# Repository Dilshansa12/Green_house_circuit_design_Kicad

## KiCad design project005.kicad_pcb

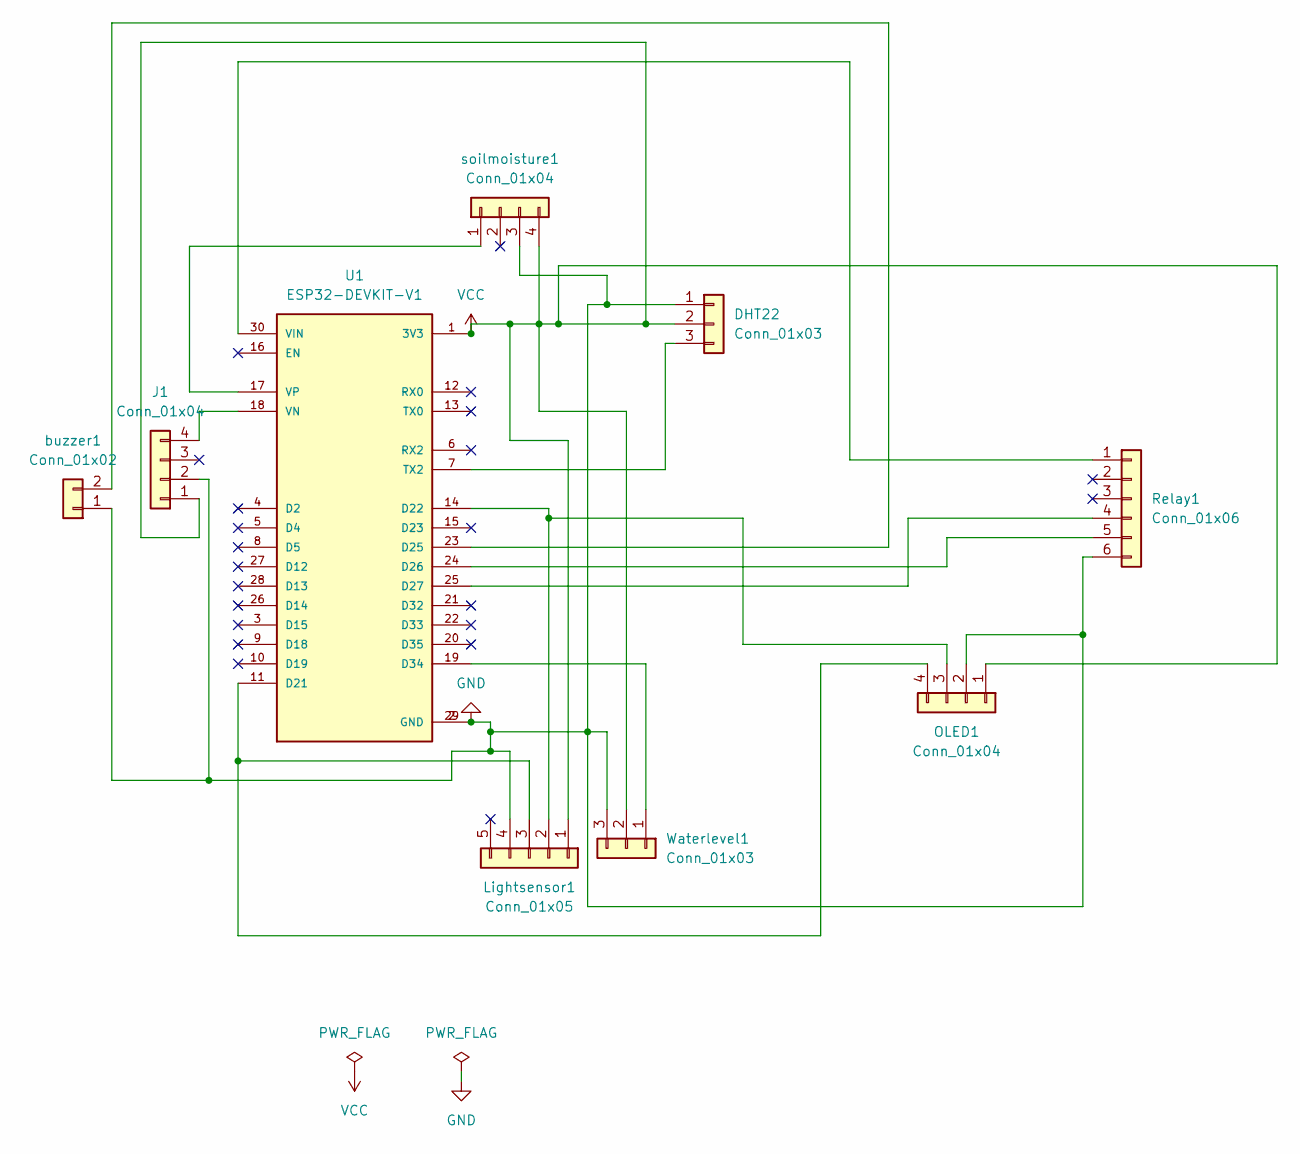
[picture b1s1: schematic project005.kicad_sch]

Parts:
DHT22: Conn_01x03; PinSocket_1x03_P2.54mm_Vertical
J1: Conn_01x04; PinSocket_1x04_P2.54mm_Vertical
Lightsensor1: Conn_01x05; PinSocket_1x05_P2.54mm_Vertical
OLED1: Conn_01x04; PinSocket_1x04_P2.54mm_Vertical
Relay1: Conn_01x06; PinSocket_1x06_P2.54mm_Vertical
U1: ESP32-DEVKIT-V1; MODULE_ESP32_DEVKIT_V1; PARTREV N/A
Waterlevel1: Conn_01x03; PinHeader_1x03_P2.54mm_Vertical
buzzer1: Conn_01x02; PinHeader_1x02_P2.54mm_Vertical
soilmoisture1: Conn_01x04; PinHeader_1x04_P2.54mm_Vertical

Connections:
GND: DHT22.1, J1.2, Lightsensor1.4, OLED1.2, Relay1.6, U1.2 (GND), U1.29 (GND), Waterlevel1.3, buzzer1.1, soilmoisture1.3
unnamed: DHT22.3, U1.7 (TX2)
unnamed: J1.4, U1.18 (VN)
unnamed: Lightsensor1.2, OLED1.3, U1.14 (D22)
unnamed: Lightsensor1.3, OLED1.4, U1.11 (D21)
unnamed: Relay1.1, U1.30 (VIN)
unnamed: Relay1.4, U1.25 (D27)
unnamed: Relay1.5, U1.24 (D26)
unnamed: U1.23 (D25), buzzer1.2
unnamed: U1.19 (D34), Waterlevel1.1
unnamed: U1.17 (VP), soilmoisture1.1
VCC: DHT22.2, J1.1, Lightsensor1.1, OLED1.1, U1.1 (3V3), Waterlevel1.2, soilmoisture1.4

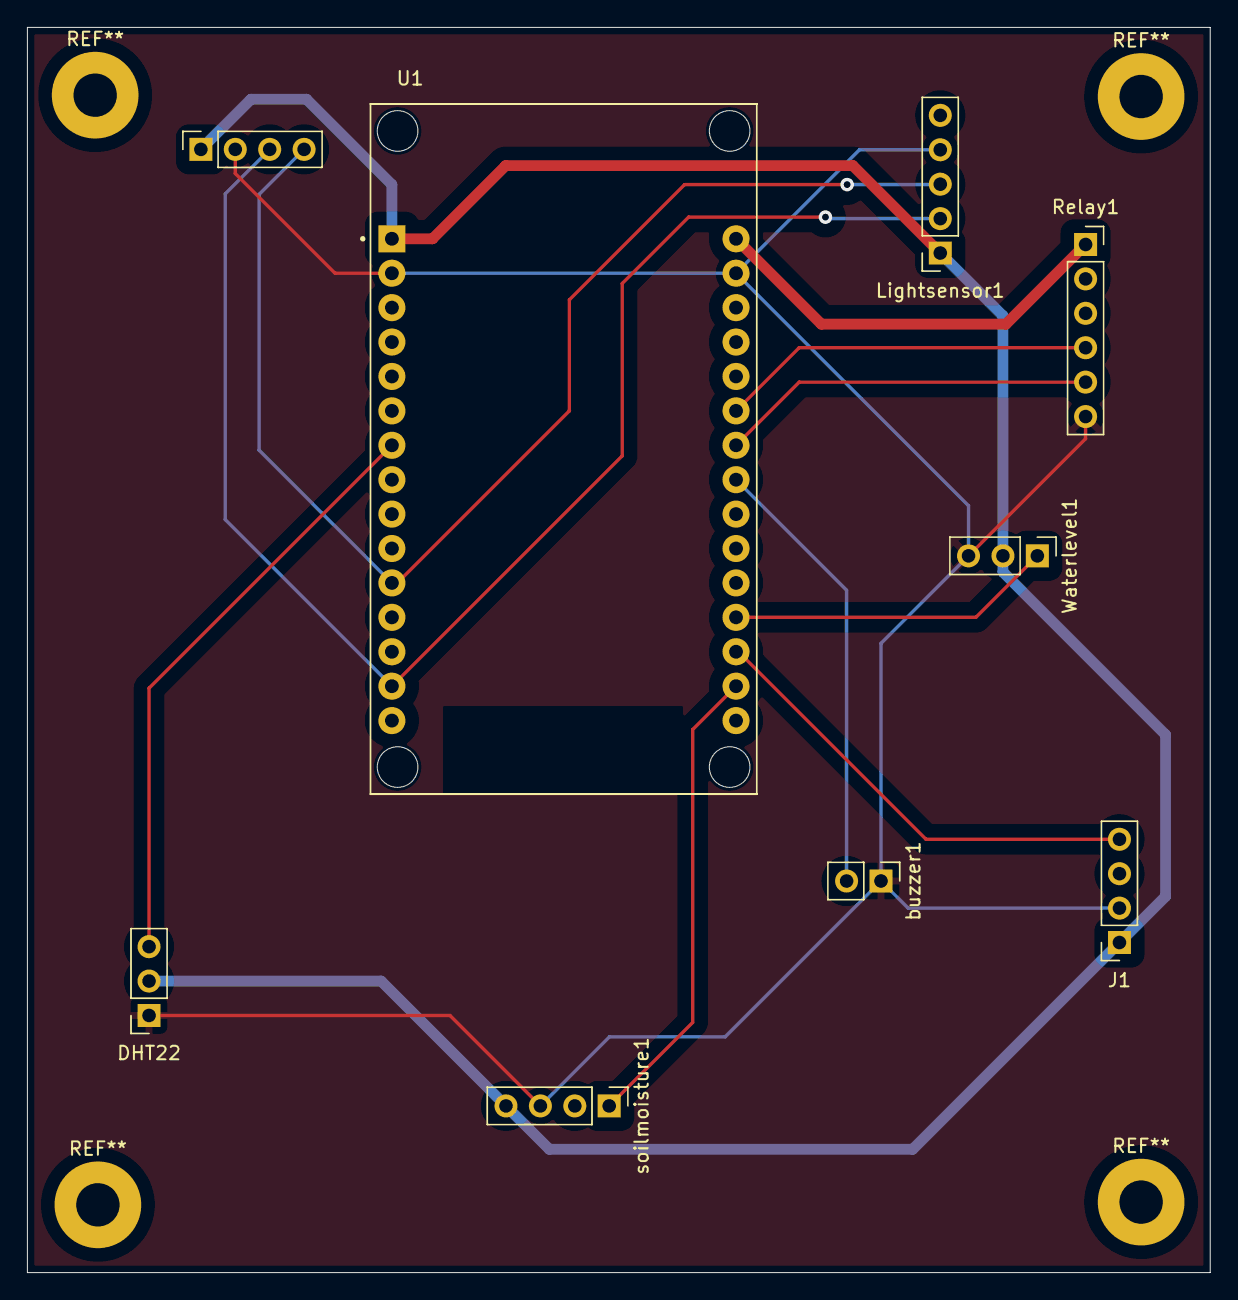
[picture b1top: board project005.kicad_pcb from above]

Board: 2 copper layers, 87.3 x 91.9 mm, 9 parts (0 on the bottom side), 12 nets.

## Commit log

2025-11-16 Initial KiCad project upload
2025-11-16 This is 3D models in needed
